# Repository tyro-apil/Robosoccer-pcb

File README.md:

# Kicad-designs
circuit designs i have made in kicad

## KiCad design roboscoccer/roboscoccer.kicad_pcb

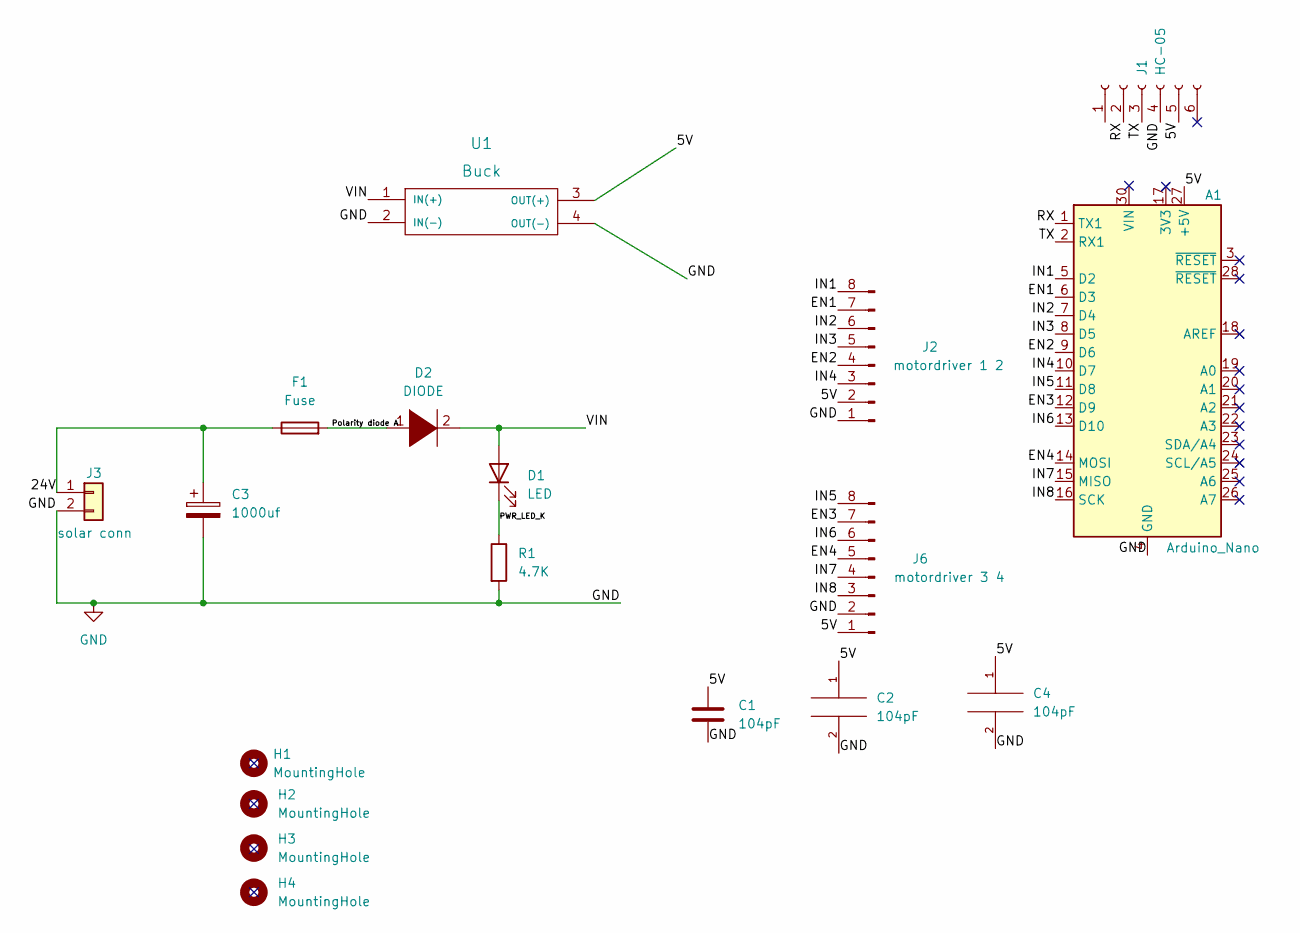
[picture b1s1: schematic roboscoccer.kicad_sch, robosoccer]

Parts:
A1: Arduino_Nano
C1, C2, C4: 104pF; Capacitor_Disc_Small
C3: 1000uf; Capacitor_1000uF
D1: LED; LED_D3.0mm
D2: DIODE; Diode_Medium
F1: Fuse; Fuse_Holder
H1, H2, H3, H4: MountingHole; MountingHole_3.2mm_M3_DIN965_Pad
J1: HC-05; JST_EH_B6B-EH-A_1x06_P2.50mm_Vertical
J2: motordriver 1 2; JST_EH_B8B-EH-A_1x08_P2.50mm_Vertical
J3: solar conn; Solar_Connector
J6: motordriver 3 4; JST_EH_B8B-EH-A_1x08_P2.50mm_Vertical
R1: 4.7K; Resistor_small
U1: Buck; Buck_Regulator

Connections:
/5V: A1.27 (+5V), C1.1, C2.1, C4.1, J1.5, J2.2, J6.1, U1.3 (OUT(+))
/24V: C3.1, F1.1, J3.1
/EN1: A1.6 (D3), J2.7
/EN2: A1.9 (D6), J2.4
/EN3: A1.12 (D9), J6.7
/EN4: A1.14 (MOSI), J6.5
/IN1: A1.5 (D2), J2.8
/IN2: A1.7 (D4), J2.6
/IN3: A1.8 (D5), J2.5
/IN4: A1.10 (D7), J2.3
/IN5: A1.11 (D8), J6.8
/IN6: A1.13 (D10), J6.6
/IN7: A1.15 (MISO), J6.4
/IN8: A1.16 (SCK), J6.3
/PWR_LED_K: D1.1 (K), R1.1
/Polarity diode A: D2.1 (K), F1.2
/RX: A1.1 (TX1), J1.2
/TX: A1.2 (RX1), J1.3
/VIN: D1.2 (A), D2.2 (A), U1.1 (IN(+))
GND: A1.4 (GND), A1.29 (GND), C1.2, C2.2, C3.2, C4.2, J1.4, J2.1, J3.2, J6.2, R1.2, U1.2 (IN(-)), U1.4 (OUT(-))

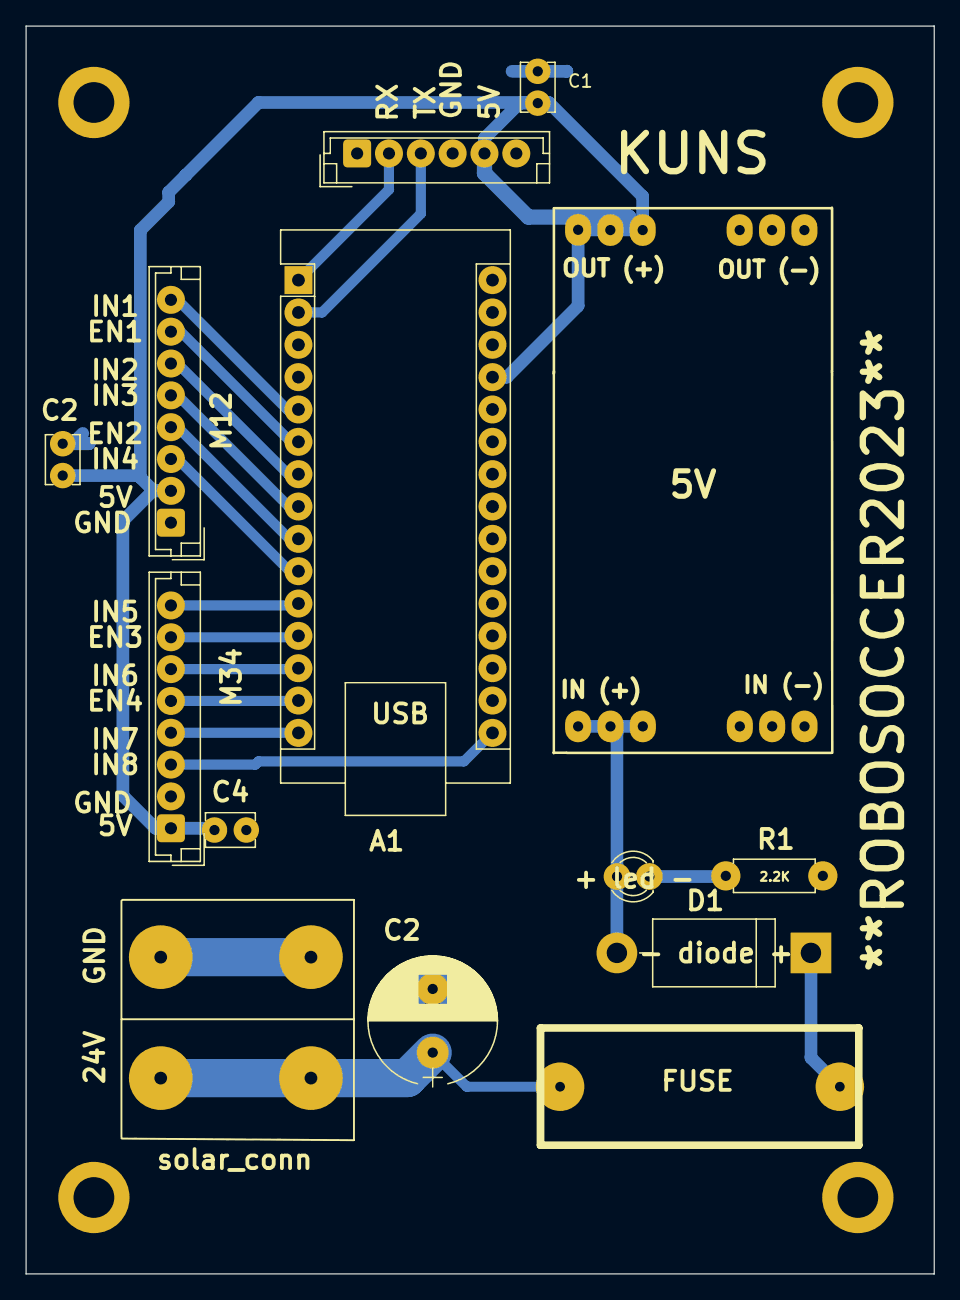
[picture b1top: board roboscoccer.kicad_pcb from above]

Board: 2 copper layers, 71.3 x 98.0 mm, 18 parts (0 on the bottom side), 20 nets.

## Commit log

2023-01-29 roboscoccer.kicad_sch-bak
2023-01-29 Create roboscoccer.kicad_sch-bak
2023-02-03 robosocccer final design
2023-02-03 final design
2023-05-02 Position of power supply components changed
2023-05-02 Decoupling capacitors placement near 5V power output
